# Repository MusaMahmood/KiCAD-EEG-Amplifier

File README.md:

# KiCAD-EEG-Amplifier
Models for amplification modules for EEG Amps.

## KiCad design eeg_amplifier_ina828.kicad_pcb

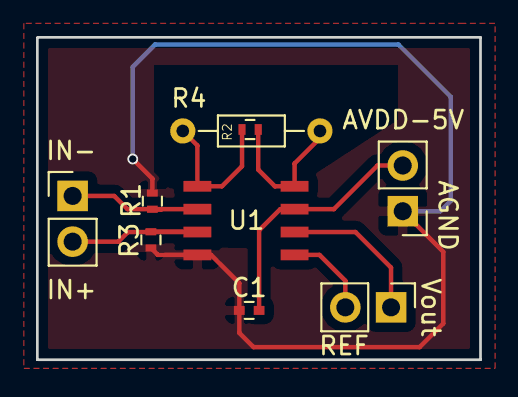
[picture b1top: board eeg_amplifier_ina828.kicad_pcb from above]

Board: 2 copper layers, 24.6 x 17.9 mm, 9 parts (0 on the bottom side), 8 nets.

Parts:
C1: C; C_0402
J1, J2, J3: CONN_01X02; Pin_Header_Straight_1x02_Pitch2.54mm
R1, R3, R4: R; R_0402
R2: R; R_Axial_DIN0204_L3.6mm_D1.6mm_P7.62mm_Horizontal
U1: INA828; SOIC_8_4.9mm_x_3.91

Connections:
/IN+: J1.2, R3.2, U1.3
/IN-: J1.1, R1.2, U1.2
/REF: J3.2, U1.5
/VOUT: J3.1, U1.6
AVDD: C1.2, J2.2, U1.7
AVSS: C1.1, J2.1, R1.1, R3.1, U1.4
unnamed: R2.1, R4.1, U1.1
unnamed: R2.2, R4.2, U1.8

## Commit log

2017-11-05 Initial Commit.
2017-11-06 Added library, updated schematic and PCB design for breakout board.
2017-11-06 Final changes for amp setup, with PCB.
2017-11-19 Updated schematic for validated values in ECG testing.
